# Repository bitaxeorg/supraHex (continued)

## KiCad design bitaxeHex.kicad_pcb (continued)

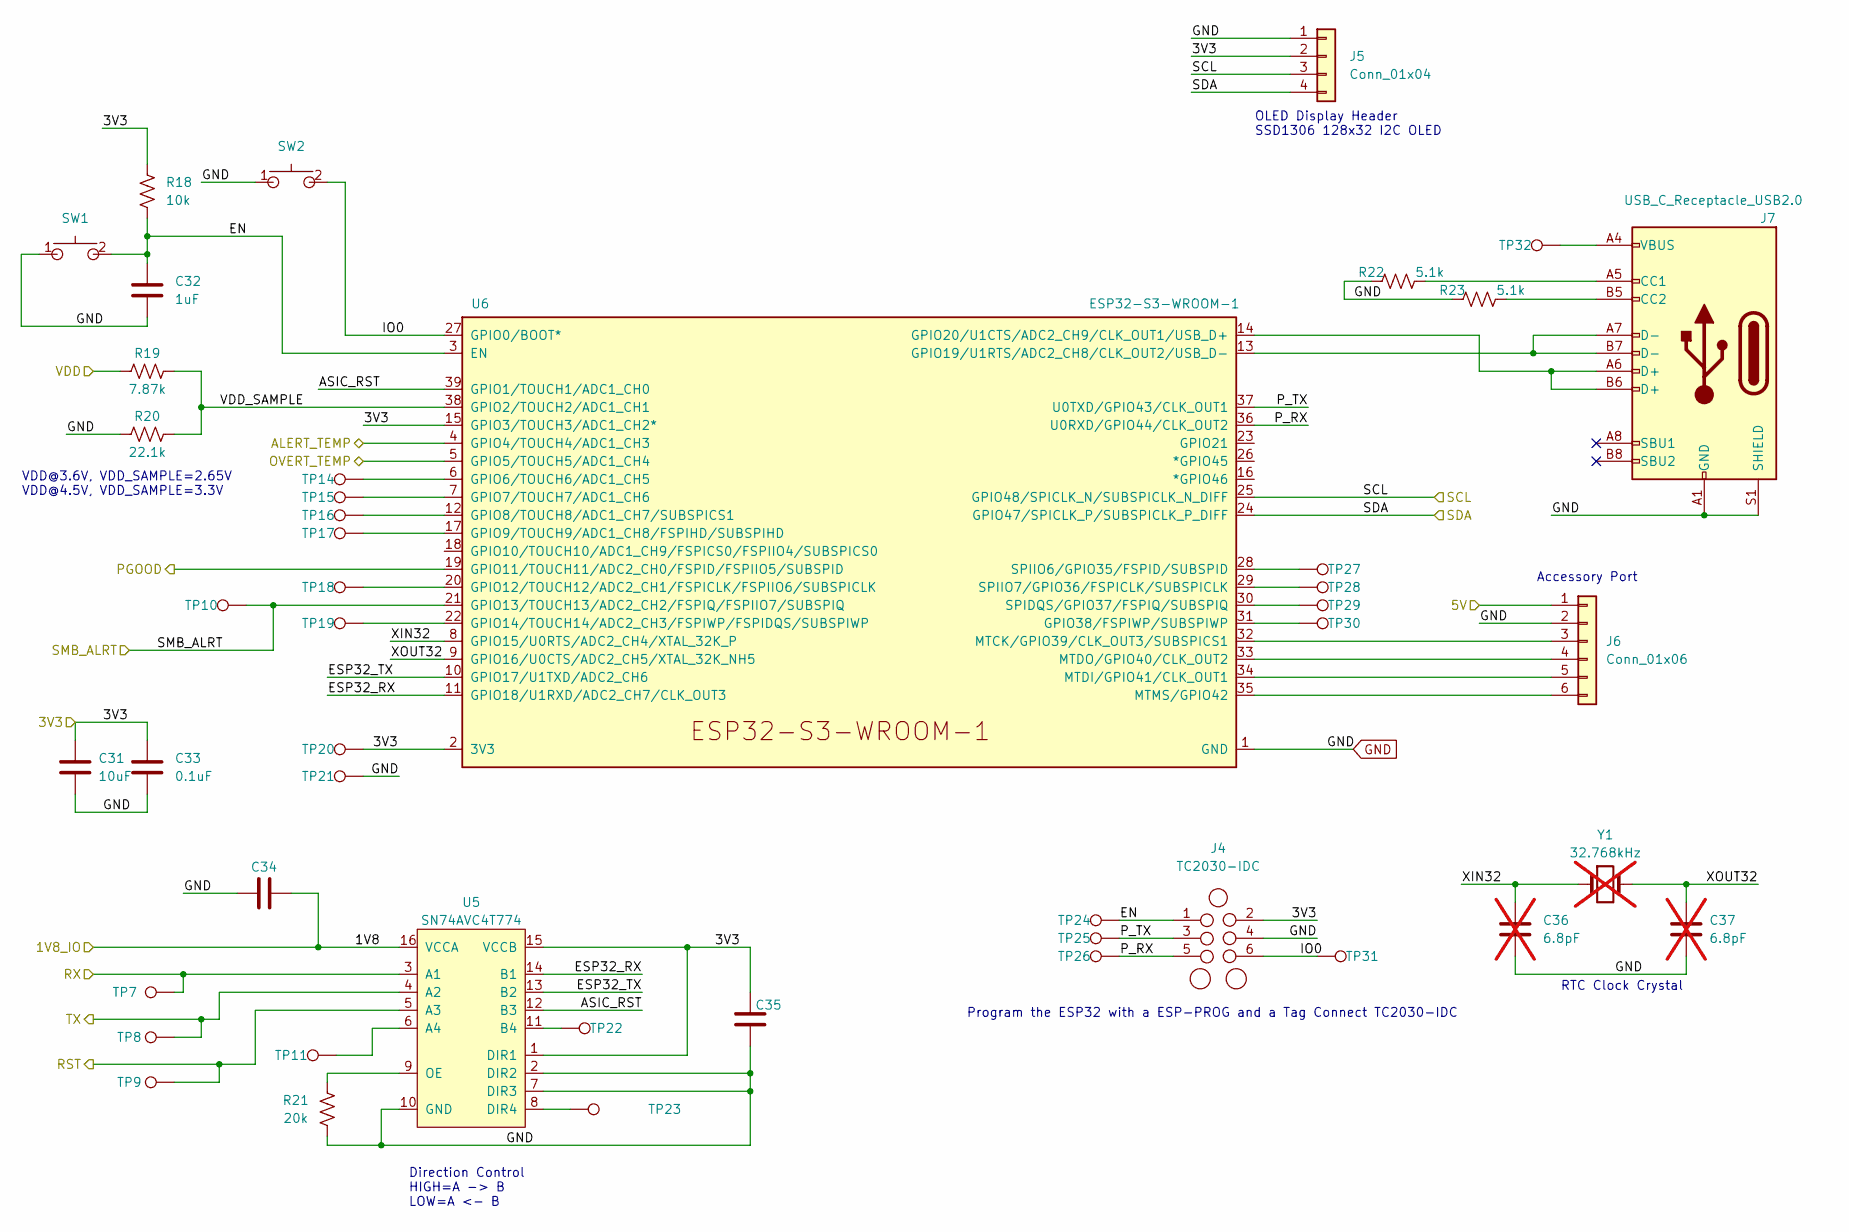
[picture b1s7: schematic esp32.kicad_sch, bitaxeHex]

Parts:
C31: 10uF; C_0805_2012Metric; PARTNO GRM21BR61H106ME43L
C32: 1uF; C_0402_1005Metric; PARTNO EMK105BJ105MV-F
C33: 0.1uF; C_0402_1005Metric; PARTNO KGM05AR71C104KH
C34, C35: 311-3342-1-ND; C_0402_1005Metric; PARTNO KGM05AR71C104KH
C36, C37: 6.8pF; C_0402_1005Metric; PARTNO C0402C689C5GAC7867; not fitted
J4: TC2030-IDC; Tag-Connect_TC2030-IDC-NL_2x03_P1.27mm_Vertical
J5: Conn_01x04; PinHeader_1x04_P2.54mm_Vertical
J6: Conn_01x06; PinHeader_1x06_P2.54mm_Vertical
J7: USB_C_Receptacle_USB2.0; USB_C_Receptacle_GCT_USB4105-xx-A_16P_TopMnt_Horizontal; PARTNO USB4105-GF-A
R18: 10k; R_0402_1005Metric; PARTNO RC0402JR-0710KL
R19: 7.87k; R_0402_1005Metric; PARTNO RC0402FR-077K87L
R20: 22.1k; R_0402_1005Metric; PARTNO RC0402FR-0722K1L
R21: 20k; R_0402_1005Metric; PARTNO RC0402FR-0720KL
R22, R23: 5.1k; R_0402_1005Metric; PARTNO RC0402FR-135K1L
SW1, SW2: SWITCH-SPST; TL3340-switch; PARTNO TL3340AF160QG
TP7, TP8, TP9, TP10, TP11, TP14, TP15, TP16, TP17, TP18, TP19, TP20, TP21, TP22, TP23, TP24, TP25, TP26, TP27, TP28, TP29, TP30, TP31, TP32: TestPoint; TestPoint_Pad_D1.0mm
U5: SN74AVC4T774; TSSOP-16_4.4x5mm_P0.65mm; PARTNO SN74AVC4T774PWR
U6: ESP32-S3-WROOM-1; ESP32-S3-WROOM-1U; PARTNO ESP32-S3-WROOM-1U-N16R8
Y1: 32.768kHz; SC32S-7PF20PPM; PARTNO SC32S-7PF20PPM; not fitted

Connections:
/3V3: C31.1, C33.1, C35.1, J4.2, J5.2, R18.1, TP20.1, U5.1 (DIR1), U5.15 (VCCB), U6.2 (3V3), U6.15 (GPIO3/TOUCH3/ADC1_CH2*); also elsewhere on the board
/5V: J6.1; also elsewhere on the board
/CI: TP8.1, U5.4 (A2); also elsewhere on the board
/ESP32/1V8: C34.2, U5.16 (VCCA)
/ESP32/ALERT_TEMP: U6.4 (GPIO4/TOUCH4/ADC1_CH3); also elsewhere on the board
/ESP32/ASIC_RST: U5.12 (B3), U6.39 (GPIO1/TOUCH1/ADC1_CH0)
/ESP32/EN: C32.1, J4.1, R18.2, SW1.2, TP24.1, U6.3 (EN)
/ESP32/ESP32_RX: U5.14 (B1), U6.11 (GPIO18/U1RXD/ADC2_CH7/CLK_OUT3)
/ESP32/ESP32_TX: U5.13 (B2), U6.10 (GPIO17/U1TXD/ADC2_CH6)
/ESP32/IO0: J4.6, SW2.2, TP31.1, U6.27 (GPIO0/BOOT*)
/ESP32/OVERT_TEMP: U6.5 (GPIO5/TOUCH5/ADC1_CH4); also elsewhere on the board
/ESP32/P_RX: J4.5, TP26.1, U6.36 (U0RXD/GPIO44/CLK_OUT2)
/ESP32/P_TX: J4.3, TP25.1, U6.37 (U0TXD/GPIO43/CLK_OUT1)
/ESP32/VDD_SAMPLE: R19.1, R20.2, U6.38 (GPIO2/TOUCH2/ADC1_CH1)
/ESP32/XIN32: C36.1, U6.8 (GPIO15/U0RTS/ADC2_CH4/XTAL_32K_P), Y1.1
/ESP32/XOUT32: C37.1, U6.9 (GPIO16/U0CTS/ADC2_CH5/XTAL_32K_NH5), Y1.2
/NRSTI: TP9.1, U5.5 (A3); also elsewhere on the board
/Power/PGOOD: U6.19 (GPIO11/TOUCH11/ADC2_CH0/FSPID/FSPIIO5/S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); also elsewhere on the board
/RO: TP7.1, U5.3 (A1); also elsewhere on the board
/SCL: J5.3, U6.25 (GPIO48/SPICLK_N/SUBSPICLK_N_DIFF); also elsewhere on the board
/SDA: J5.4, U6.24 (GPIO47/SPICLK_P/SUBSPICLK_P_DIFF); also elsewhere on the board
/SMB_ALRT: TP10.1, U6.21 (GPIO13/TOUCH13/ADC2_CH2/FSPIQ/FSPIIO7/S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); also elsewhere on the board
/VDD: R19.2; also elsewhere on the board
GND: C31.2, C32.2, C33.2, C34.1, C35.2, C36.2, C37.2, J4.4, J5.1, J6.2, J7.A1 (GND), J7.A12 (GND), J7.B1 (GND), J7.B12 (GND), J7.S1 (SHIELD), R20.1, R21.1, R22.1, R23.1, SW1.1, SW2.1, TP21.1, U5.2 (DIR2), U5.7 (DIR3), U5.10 (GND), U6.1 (GND), U6.40 (GND), U6.41 (GND); also elsewhere on the board
unnamed: J6.3, U6.32 (MTCK/GPIO39/CLK_OUT3/SUBSPICS1)
unnamed: J6.4, U6.33 (MTDO/GPIO40/CLK_OUT2)
unnamed: J6.5, U6.34 (MTDI/GPIO41/CLK_OUT1)
unnamed: J6.6, U6.35 (MTMS/GPIO42)
unnamed: J7.A5 (CC1), R22.2
unnamed: J7.B5 (CC2), R23.2
unnamed: J7.A4 (VBUS), J7.A9 (VBUS), J7.B4 (VBUS), J7.B9 (VBUS), TP32.1
unnamed: TP11.1, U5.6 (A4)
unnamed: TP22.1, U5.11 (B4)
unnamed: TP23.1, U5.8 (DIR4)
unnamed: R21.2, U5.9 (OE)
unnamed: TP14.1, U6.6 (GPIO6/TOUCH6/ADC1_CH5)
unnamed: TP15.1, U6.7 (GPIO7/TOUCH7/ADC1_CH6)
unnamed: TP16.1, U6.12 (GPIO8/TOUCH8/ADC1_CH7/SUBSPICS1)
unnamed: TP17.1, U6.17 (GPIO9/TOUCH9/ADC1_CH8/FSPIHD/SUBSPIHD)
unnamed: TP18.1, U6.20 (GPIO12/TOUCH12/ADC2_CH1/FSPICLK/FSPIIO6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)
unnamed: TP19.1, U6.22 (GPIO14/TOUCH14/ADC2_CH3/FSPIWP/FSPIDQS/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)
unnamed: J7.A7 (D-), J7.B7 (D-), U6.13 (GPIO19/U1RTS/ADC2_CH8/CLK_OUT2/USB_D-)
unnamed: J7.A6 (D+), J7.B6 (D+), U6.14 (GPIO20/U1CTS/ADC2_CH9/CLK_OUT1/USB_D+)
unnamed: TP30.1, U6.31 (GPIO38/FSPIWP/SUBSPIWP)
unnamed: TP29.1, U6.30 (SPIDQS/GPIO37/FSPIQ/SUBSPIQ)
unnamed: TP27.1, U6.28 (SPIIO6/GPIO35/FSPID/SUBSPID)
unnamed: TP28.1, U6.29 (SPIIO7/GPIO36/FSPICLK/SUBSPICLK)

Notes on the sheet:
OLED Display Header SSD1306 128x32 I2C OLED
RTC Clock Crystal
Accessory Port
Program the ESP32 with a ESP-PROG and a Tag Connect TC2030-IDC
VDD@3.6V, VDD_SAMPLE=2.65V VDD@4.5V, VDD_SAMPLE=3.3V
Direction Control HIGH=A -> B LOW=A <- B

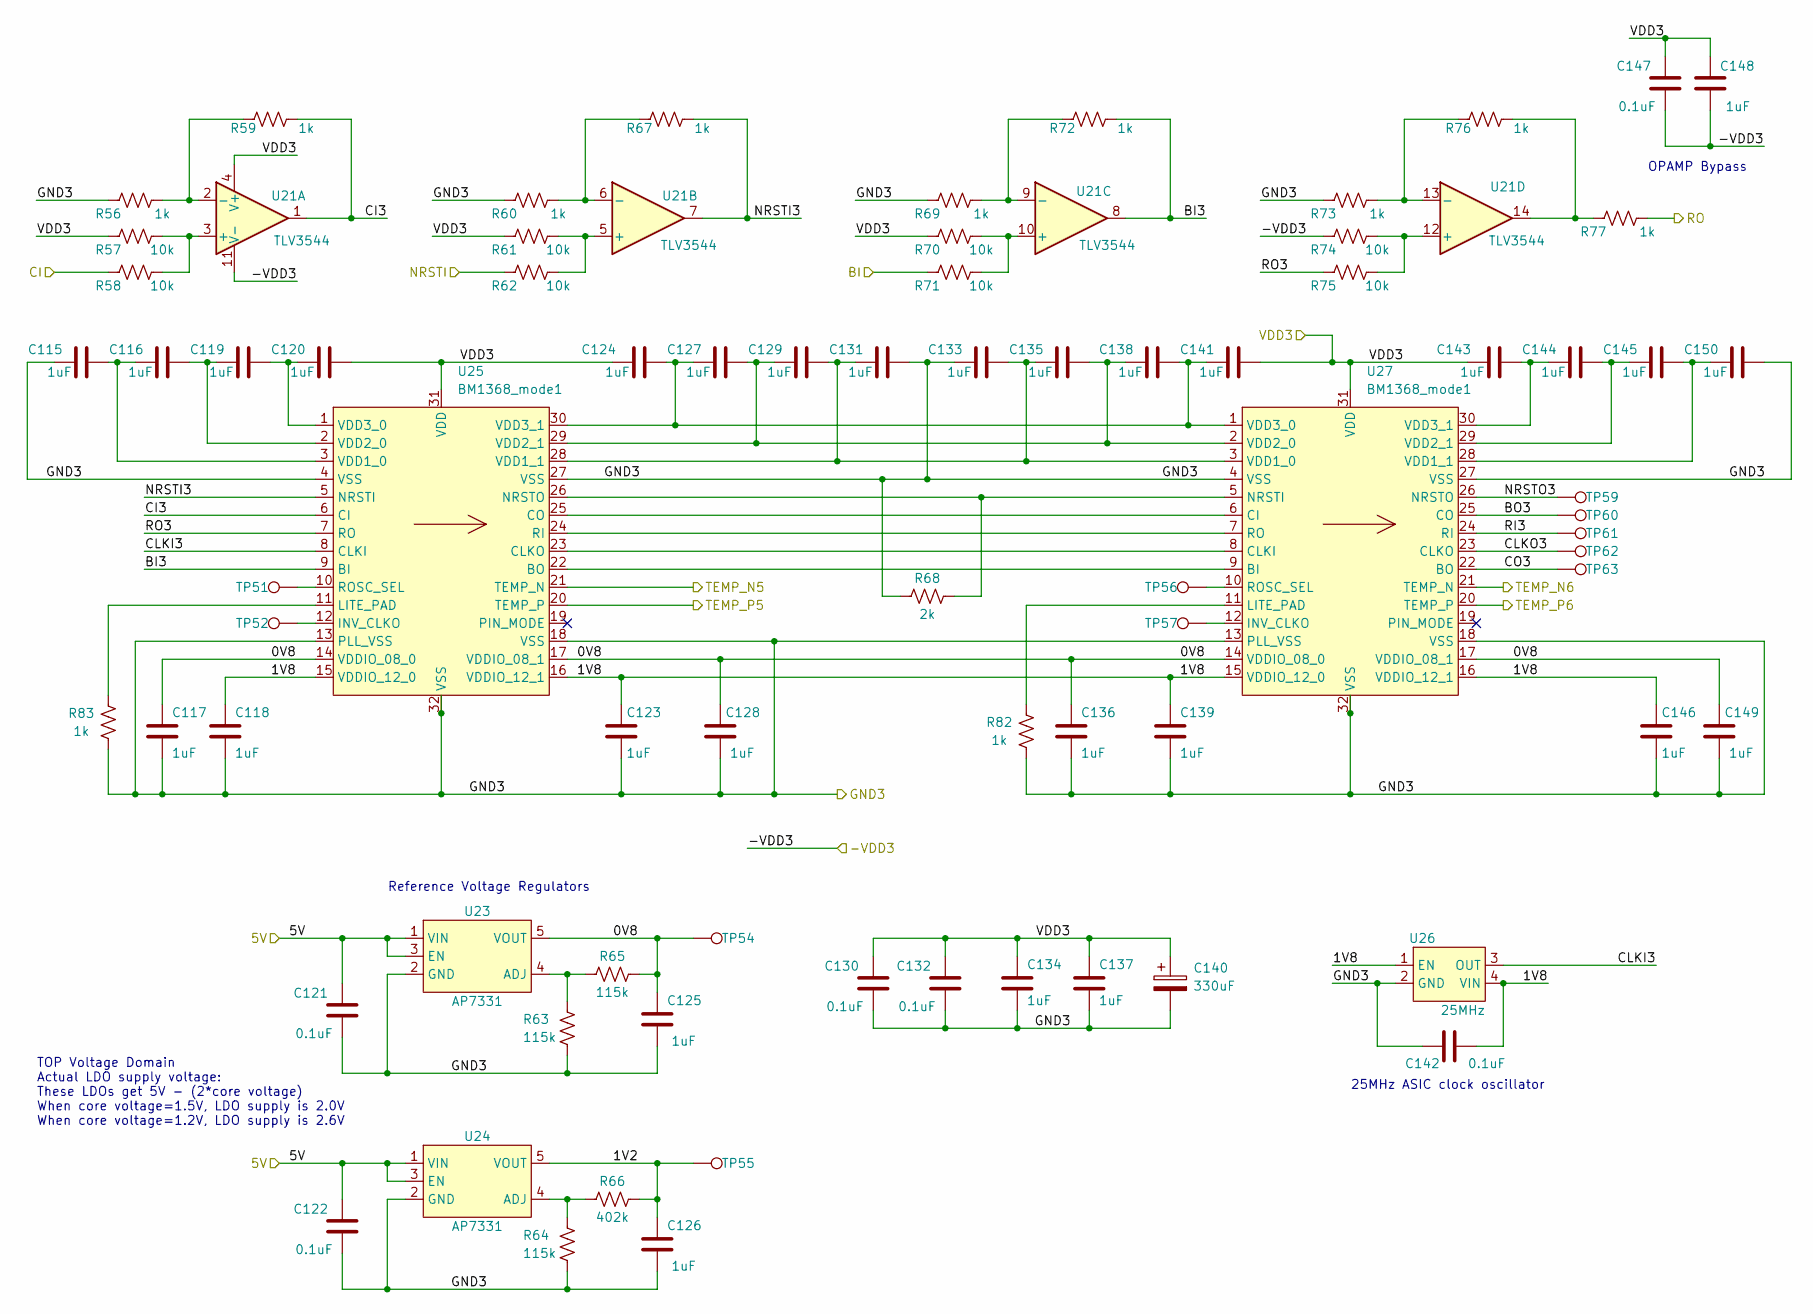
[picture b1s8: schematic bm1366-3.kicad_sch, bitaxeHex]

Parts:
C115, C116, C117, C118, C119, C120, C123, C124, C125, C126, C127, C128, C129, C131, C133, C134, C135, C136, C137, C138, C139, C141, C143, C144, C145, C146, C148, C149, C150: 1uF; C_0402_1005Metric; PARTNO EMK105BJ105MV-F
C121, C122, C130, C132, C142, C147: 0.1uF; C_0402_1005Metric; PARTNO KGM05AR71C104KH
C140: 330uF; CP_EIA-7343-31_Kemet-D_Pad2.25x2.55mm_HandSolder; PARTNO 293D337X9010E2TE3
R56, R59, R60, R67, R69, R72, R73, R76, R77, R82, R83: 1k; R_0402_1005Metric; PARTNO RC0402FR-071KL
R57, R58, R61, R62, R70, R71, R74, R75: 10k; R_0402_1005Metric; PARTNO RC0402JR-0710KL
R63, R64, R65: 115k; R_0402_1005Metric; PARTNO RC0402FR-07115KL
R66: 402k; R_0402_1005Metric; PARTNO RC0402FR-07402KL
R68: 2k; R_0402_1005Metric; PARTNO RT0402BRD072KL
TP51, TP52, TP54, TP55, TP56, TP57: TestPoint; TestPoint_Pad_D1.0mm
TP59, TP60, TP61, TP62, TP63: TestPoint; TestPoint_Pad_D1.5mm
U21: TLV3544; TSSOP-14_4.4x5mm_P0.65mm; PARTNO TLV3544IPWR
U23, U24: AP7331; TSOT-23-5; PARTNO AP7331-WG-7
U25, U27: BM1368_mode1; BM1368
U26: 25MHz; O 25,0-JO32-B-1V3-1-T1-LF; PARTNO O 25,0-JO32-B-1V3-1-T1-LF

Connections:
/5V: C121.2, C122.2, U23.1 (VIN), U23.3 (EN), U24.1 (VIN), U24.3 (EN); also elsewhere on the board
/BM1368-1/VDD1: C147.1, C148.1, R74.1, U21.11 (V-); also elsewhere on the board
/BM1368-2/BO: R71.1; also elsewhere on the board
/BM1368-2/CO: R58.1; also elsewhere on the board
/BM1368-2/NRSTO: R62.1; also elsewhere on the board
/BM1368-2/RI: R77.1; also elsewhere on the board
/BM1368-2/VDD2: C115.1, C117.2, C118.2, C121.1, C122.1, C123.2, C125.2, C126.2, C128.2, C130.1, C131.2, C132.1, C133.1, C134.2, C136.2, C137.2, C139.2, C140.2, C142.2, C146.2, C149.2, C150.2, R56.2, R60.2, R63.1, R64.1, R68.1, R69.2, R73.2, R82.1, R83.1, U23.2 (GND), U24.2 (GND), U25.4 (VSS), U25.13 (PLL_VSS), U25.18 (VSS), U25.27 (VSS), U25.32 (VSS), U26.2 (GND), U27.4 (VSS), U27.13 (PLL_VSS), U27.18 (VSS), U27.27 (VSS), U27.32 (VSS); also elsewhere on the board
/BM1368-3/0V8: C117.1, C125.1, C128.1, C136.1, C149.1, R65.2, TP54.1, U23.5 (VOUT), U25.14 (VDDIO_08_0), U25.17 (VDDIO_08_1), U27.14 (VDDIO_08_0), U27.17 (VDDIO_08_1)
/BM1368-3/BI3: R72.1, U21.8, U25.9 (BI)
/BM1368-3/BO3: TP60.1, U27.25 (CO)
/BM1368-3/CI3: R59.1, U21.1, U25.6 (CI)
/BM1368-3/CLKI3: U25.8 (CLKI), U26.3 (OUT)
/BM1368-3/CLKO3: TP62.1, U27.23 (CLKO)
/BM1368-3/CO3: TP63.1, U27.22 (BO)
/BM1368-3/NRSTI3: R67.1, U21.7, U25.5 (NRSTI)
/BM1368-3/NRSTO3: TP59.1, U27.26 (NRSTO)
/BM1368-3/RI3: TP61.1, U27.24 (RI)
/BM1368-3/RO3: R75.1, U25.7 (RO)
/BM1368-3/TEMP_N5: U25.21 (TEMP_N); also elsewhere on the board
/BM1368-3/TEMP_N6: U27.21 (TEMP_N); also elsewhere on the board
/BM1368-3/TEMP_P5: U25.20 (TEMP_P); also elsewhere on the board
/BM1368-3/TEMP_P6: U27.20 (TEMP_P); also elsewhere on the board
/VDD: C120.2, C124.1, C130.2, C132.2, C134.1, C137.1, C140.1, C141.2, C143.1, C147.2, C148.2, R57.1, R61.1, R70.1, U21.4 (V+), U25.31 (VDD), U27.31 (VDD); also elsewhere on the board
unnamed: R76.1, R77.2, U21.14
unnamed: R57.2, R58.2, U21.3 (+)
unnamed: R56.1, R59.2, U21.2 (-)
unnamed: R61.2, R62.2, U21.5 (+)
unnamed: R60.1, R67.2, U21.6 (-)
unnamed: R70.2, R71.2, U21.10 (+)
unnamed: R69.1, R72.2, U21.9 (-)
unnamed: R74.2, R75.2, U21.12 (+)
unnamed: R73.1, R76.2, U21.13 (-)
unnamed: R63.2, R65.1, U23.4 (ADJ)
unnamed: R64.2, R66.2, U24.4 (ADJ)
unnamed: U25.22 (BO), U27.9 (BI)
unnamed: U25.23 (CLKO), U27.8 (CLKI)
unnamed: U25.25 (CO), U27.6 (CI)
unnamed: TP52.1, U25.12 (INV_CLKO)
unnamed: R83.2, U25.11 (LITE_PAD)
unnamed: R68.2, U25.26 (NRSTO), U27.5 (NRSTI)
unnamed: U25.24 (RI), U27.7 (RO)
unnamed: TP51.1, U25.10 (ROSC_SEL)
unnamed: C115.2, C116.1, U25.3 (VDD1_0)
unnamed: C129.2, C131.1, C133.2, C135.1, U25.28 (VDD1_1), U27.3 (VDD1_0)
unnamed: C116.2, C119.1, U25.2 (VDD2_0)
unnamed: C127.2, C129.1, C135.2, C138.1, U25.29 (VDD2_1), U27.2 (VDD2_0)
unnamed: C119.2, C120.1, U25.1 (VDD3_0)
unnamed: C124.2, C127.1, C138.2, C141.1, U25.30 (VDD3_1), U27.1 (VDD3_0)
unnamed: TP57.1, U27.12 (INV_CLKO)
unnamed: R82.2, U27.11 (LITE_PAD)
unnamed: TP56.1, U27.10 (ROSC_SEL)
unnamed: C145.2, C150.1, U27.28 (VDD1_1)
unnamed: C144.2, C145.1, U27.29 (VDD2_1)
unnamed: C143.2, C144.1, U27.30 (VDD3_1)

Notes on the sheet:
25MHz ASIC clock oscillator
Reference Voltage Regulators
OPAMP Bypass
TOP Voltage Domain Actual LDO supply voltage: These LDOs get 5V - (2*core voltage) When core voltage=1.5V, LDO supply is 2.0V When core voltage=1.2V, LDO supply is 2.6V

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
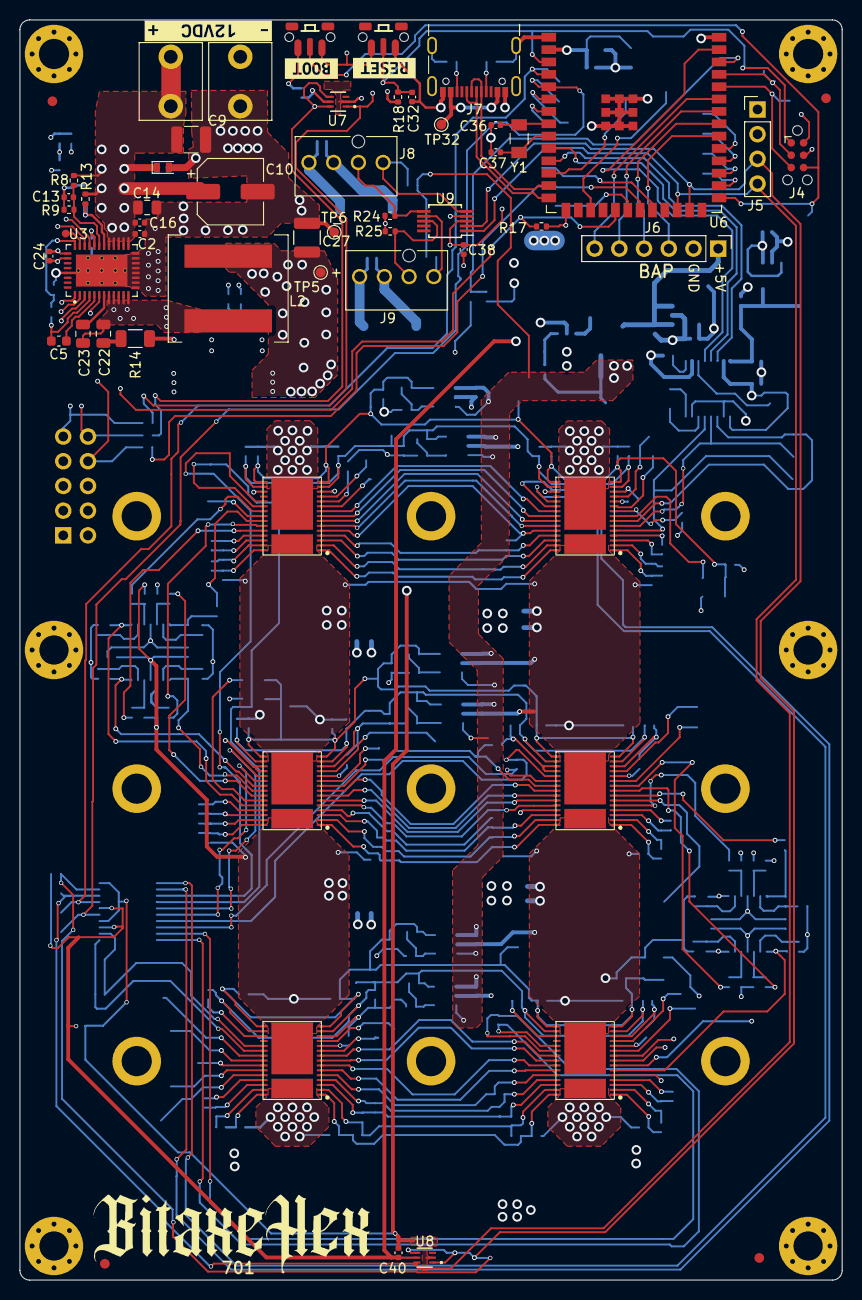
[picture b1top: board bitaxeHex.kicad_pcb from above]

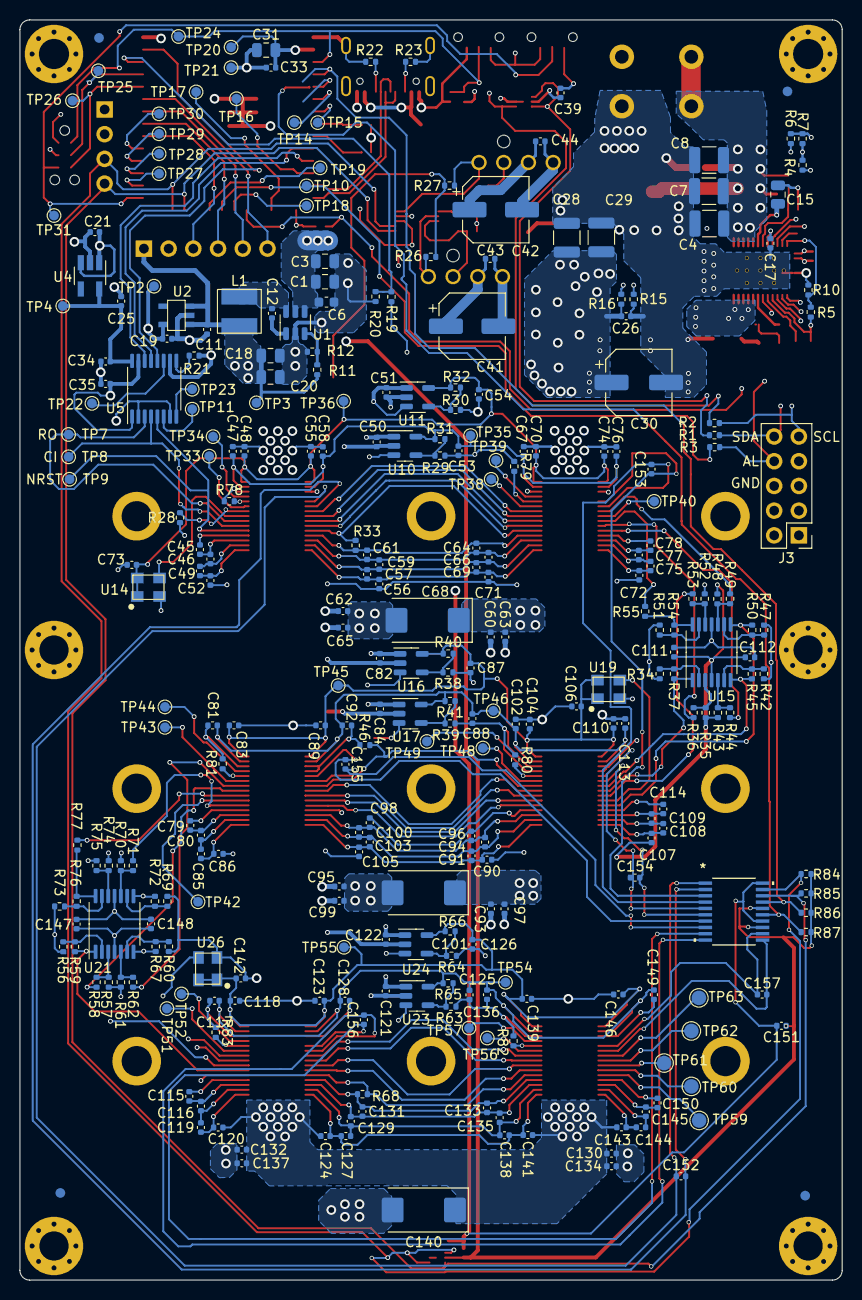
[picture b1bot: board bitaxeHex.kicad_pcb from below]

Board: 4 copper layers, 84.5 x 129.5 mm, 368 parts (293 on the bottom side), 205 nets.

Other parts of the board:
kibuzzard-65356D4E: G***; kibuzzard-65356D4E
kibuzzard-65356D5C: G***; kibuzzard-65356D5C
kibuzzard-65978662: G***; kibuzzard-65978662

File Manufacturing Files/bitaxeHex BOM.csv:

"Reference","Value","Footprint","Qty","DK","PARTNO"
"C1, C3, C18, C20, C31","10uF","Capacitor_SMD:C_0805_2012Metric","5","490-18664-1-ND","GRM21BR61H106ME43L"
"C2","4.7nF","Capacitor_SMD:C_0402_1005Metric","1","490-1309-1-ND","GRM155R71E472KA01D"
"C4, C7, C8, C9","22uF","Capacitor_SMD:C_1210_3225Metric","4","490-3889-1-ND","GRM32ER61E226KE15L"
"C5","1uF","Capacitor_SMD:C_0603_1608Metric","1","490-1550-1-ND","GRM188R60J105KA01D"
"C6","0.1uF","Capacitor_SMD:C_0603_1608Metric","1","478-KGM15BR71H104KTCT-ND","KGM15BR71H104KT"
"C10, C30","180uF","Capacitor_SMD:CP_Elec_6.3x5.9","2","P16479CT-ND","16SVPF180M"
"C11, C19, C21, C25, C32, C45, C46, C47, C48, C49, C52, C53, C54, C55, C56, C57, C58, C59, C61, C63, C64, C65, C66, C67, C69, C70, C71, C72, C74, C75, C76, C77, C78, C79, C80, C81, C83, C85, C86, C87, C88, C89, C90, C91, C92, C94, C96, C97, C98, C99, C100, C102, C103, C104, C105, C107, C108, C109, C110, C112, C113, C114, C115, C116, C117, C118, C119, C120, C123, C124, C125, C126, C127, C128, C129, C131, C133, C134, C135, C136, C137, C138, C139, C141, C143, C144, C145, C146, C148, C149, C150","1uF","Capacitor_SMD:C_0402_1005Metric","91","587-5514-1-ND","EMK105BJ105MV-F"
"C12, C33, C50, C51, C60, C62, C73, C82, C84, C93, C95, C106, C111, C121, C122, C130, C132, C142, C147, C151","0.1uF","Capacitor_SMD:C_0402_1005Metric","20","478-KGM05AR71C104KHCT-ND","KGM05AR71C104KH"
"C13","100nF","Capacitor_SMD:C_0402_1005Metric","1","490-6321-1-ND","GRM155R71A104KA01D"
"C14, C15","1uF","Capacitor_SMD:C_0805_2012Metric","2","587-1291-1-ND","TMK212BJ105KG-T"
"C16, C26","2.2nF","Capacitor_SMD:C_0402_1005Metric","2","490-8257-1-ND","GRM155R61H222KA01D"
"C17","4.7uF","Capacitor_SMD:C_0402_1005Metric","1","490-14306-1-ND","GRM155R61A475MEAAD"
"C22","1nF","Capacitor_SMD:C_0805_2012Metric","1","311-1127-1-ND","CC0805KRX7R9BB102"
"C23","100nF","Capacitor_SMD:C_0805_2012Metric","1","478-KGM21NR71E104KTCT-ND","KGM21NR71E104KT"
"C24","100pF","Capacitor_SMD:C_0402_1005Metric","1","732-7431-1-ND","885012005013"
"C27, C28, C29","47uF","Capacitor_SMD:C_1210_3225Metric","3","490-6539-1-ND","GRM32ER61C476KE15L"
"C34, C35, C38, C39, C40, C43, C44","311-3342-1-ND","Capacitor_SMD:C_0402_1005Metric","7","478-KGM05AR71C104KHCT-ND","KGM05AR71C104KH"
"C41, C42","220uF","Capacitor_SMD:CP_Elec_6.3x7.7","2","732-8422-1-ND","865080345012"
"C68, C101, C140","330uF","Capacitor_Tantalum_SMD:CP_EIA-7343-31_Kemet-D_Pad2.25x2.55mm_HandSolder","3","718-1028-1-ND","293D337X9010E2TE3"
"C152, C153, C154, C155, C156, C157","2.2nF","Capacitor_SMD:C_0402_1005Metric","6","311-1037-2-ND","CC0402KRX7R9BB222"
"D1","824045812","bitaxe:824045812","1","732-824045812CT-ND","824045812"
"J1, J2","Screw Terminal","bitaxe:7771-screw-terminal","2","36-7771-ND","36-7771"
"J3","Conn_02x05_Odd_Even","Connector_PinHeader_2.54mm:PinHeader_2x05_P2.54mm_Vertical","1","",""
"J6","Conn_01x06","Connector_PinHeader_2.54mm:PinHeader_1x06_P2.54mm_Vertical","1","",""
"J7","USB_C_Receptacle_USB2.0","Connector_USB:USB_C_Receptacle_GCT_USB4105-xx-A_16P_TopMnt_Horizontal","1","2073-USB4105-GF-ACT-ND","USB4105-GF-A"
"J8, J9","Conn_01x04","bitaxe:470531000","2","WM4330-ND","0470531000"
"L1","8.2 uH","bitaxe:74438357082","1","732-11745-1-ND","78438357082"
"L2","680nH","Inductor_SMD:L_Coilcraft_XAL1010-XXX","1","2457-XAL1010-681MED-ND","XAL1010-681MED"
"R1, R2, R3","0R","Resistor_SMD:R_0402_1005Metric","3","311-0.0JRCT-ND","RC0402JR-070RL"
"R4, R5","17.8K","Resistor_SMD:R_0402_1005Metric","2","RMCF0402FT17K8CT-ND","RMCF0402FT17K8"
"R6","10k","Resistor_SMD:R_0402_1005Metric","1","RMCF0402FT10K0CT-ND","RMCF0402FT10K0"
"R7","31.6K","Resistor_SMD:R_0402_1005Metric","1","YAG3115CT-ND","RC0402FR-0731K6L"
"R8","12.7K","Resistor_SMD:R_0402_1005Metric","1","YAG2964CT-ND","RC0402FR-0712K7L"
"R9, R16","1.37K","Resistor_SMD:R_0402_1005Metric","2","YAG3035CT-ND","RC0402FR-071K37L"
"R10","26.1K","Resistor_SMD:R_0402_1005Metric","1","311-26.1KLRCT-ND","RC0402FR-0726K1L"
"R11, R29, R30, R31, R38, R39, R41, R63, R64, R65","115k","Resistor_SMD:R_0402_1005Metric","10","YAG2956CT-ND","RC0402FR-07115KL"
"R12, R20","22.1k","Resistor_SMD:R_0402_1005Metric","2","311-22.1KLRCT-ND","RC0402FR-0722K1L"
"R13","10R","Resistor_SMD:R_0402_1005Metric","1","311-10.0LRCT-ND","RC0402FR-0710RL"
"R14","1R","Resistor_SMD:R_1206_3216Metric","1","CSR1206FT1R00CT-ND","CSR1206FT1R00"
"R15","49.9R","Resistor_SMD:R_0402_1005Metric","1","311-49.9LRCT-ND","RC0402FR-0749R9L"
"R17, R18, R26, R27, R28, R35, R36, R43, R44, R48, R49, R52, R53, R57, R58, R61, R62, R70, R71, R74, R75","10k","Resistor_SMD:R_0402_1005Metric","21","311-10KJRCT-ND","RC0402JR-0710KL"
"R19","7.87k","Resistor_SMD:R_0402_1005Metric","1","311-7.87KLRCT-ND","RC0402FR-077K87L"
"R21","20k","Resistor_SMD:R_0402_1005Metric","1","311-20.0KLRCT-ND","RC0402FR-0720KL"
"R22, R23","5.1k","Resistor_SMD:R_0402_1005Metric","2","13-RC0402FR-135K1LCT-ND","RC0402FR-135K1L"
"R24, R25","5.6k","Resistor_SMD:R_0402_1005Metric","2","13-RC0402FR-135K6LCT-ND","RC0402FR-135K6L"
"R32, R40, R66","402k","Resistor_SMD:R_0402_1005Metric","3","YAG3151CT-ND","RC0402FR-07402KL"
"R33, R46, R68","2k","Resistor_SMD:R_0402_1005Metric","3","YAG2303CT-ND","RT0402BRD072KL"
"R34, R37, R42, R45, R47, R50, R51, R54, R55, R56, R59, R60, R67, R69, R72, R73, R76, R77, R78, R79, R80, R81, R82, R83","1k","Resistor_SMD:R_0402_1005Metric","24","311-1.00KLRCT-ND","RC0402FR-071KL"
"R84, R85, R86, R87","4.7k","Resistor_SMD:R_0402_1005Metric","4","YAG1446TR-ND","RT0402BRD074K7L"
"SW1, SW2","SWITCH-SPST","bitaxe:TL3340-switch","2","EG4627CT-ND","TL3340AF160QG"
"U1","LMR54410","Package_TO_SOT_SMD:SOT-23-6","1","296-LMR54410DBVRCT-ND","LMR54410FDBVR"
"U2","RT9080-33GJ5","bitaxe:RT9080-33GJ5","1","1028-1509-1-ND","RT9080-33GJ5"
"U3","TPS546D24ARVFR","bitaxe:LQFN40-CLIP","1","296-TPS546D24ARVFRCT-ND","TPS546D24ARVFR"
"U4","MIC5504-MS","Package_TO_SOT_SMD:SOT-23-5_HandSoldering","1","576-4879-1-ND","MIC5504-1.8YM5-TR"
"U5","SN74AVC4T774","Package_SO:TSSOP-16_4.4x5mm_P0.65mm","1","296-24739-1-ND","SN74AVC4T774PWR"
"U6","ESP32-S3-WROOM-1","bitaxe:ESP32-S3-WROOM-1U","1","1965-ESP32-S3-WROOM-1U-N16R8CT-ND","ESP32-S3-WROOM-1U-N16R8"
"U7, U8","TMP1075","bitaxe:SOT5X3-6_DRL_TEX","2","296-TMP1075NDRLRCT-ND","TMP1075NDRLR"
"U9","EMC2302","Package_SO:MSOP-10_3x3mm_P0.5mm","1","EMC2302-2-AIZL-CT-ND","EMC2302-2-AIZL-TR"
"U10, U11, U16, U17, U23, U24","AP7331","Package_TO_SOT_SMD:TSOT-23-5","6","AP7331-WG-7DICT-ND","AP7331-WG-7"
"U12, U25, U27, U28","BM1368_mode1","bitaxe:BM1368","4","",""
"U13, U18","BM1368_mode0","bitaxe:BM1368","2","",""
"U14, U19, U26","25MHz","bitaxe:O 25,0-JO32-B-1V3-1-T1-LF","3","1908-O250-JO32-B-1V3-1-T1-LFCT-ND","O 25,0-JO32-B-1V3-1-T1-LF"
"U15, U21","TLV3544","Package_SO:TSSOP-14_4.4x5mm_P0.65mm","2","296-45352-1-ND","TLV3544IPWR"
"U20","~","bitaxe:MAX6689UP9A+","1","MAX6689UP9A+-ND","MAX6689UP9A+"

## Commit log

2024-08-30 init 701
2024-08-30 Update LICENSE
2024-08-30 gerber
2024-08-30 update gerber
2024-09-09 -Reset to 1V8/0V8 setup -Add TVS protection
2025-03-17 updated to KiCad v9, filled in incomplete BOM and exported.
2025-03-17 change the gitignore to actually add the BOM
